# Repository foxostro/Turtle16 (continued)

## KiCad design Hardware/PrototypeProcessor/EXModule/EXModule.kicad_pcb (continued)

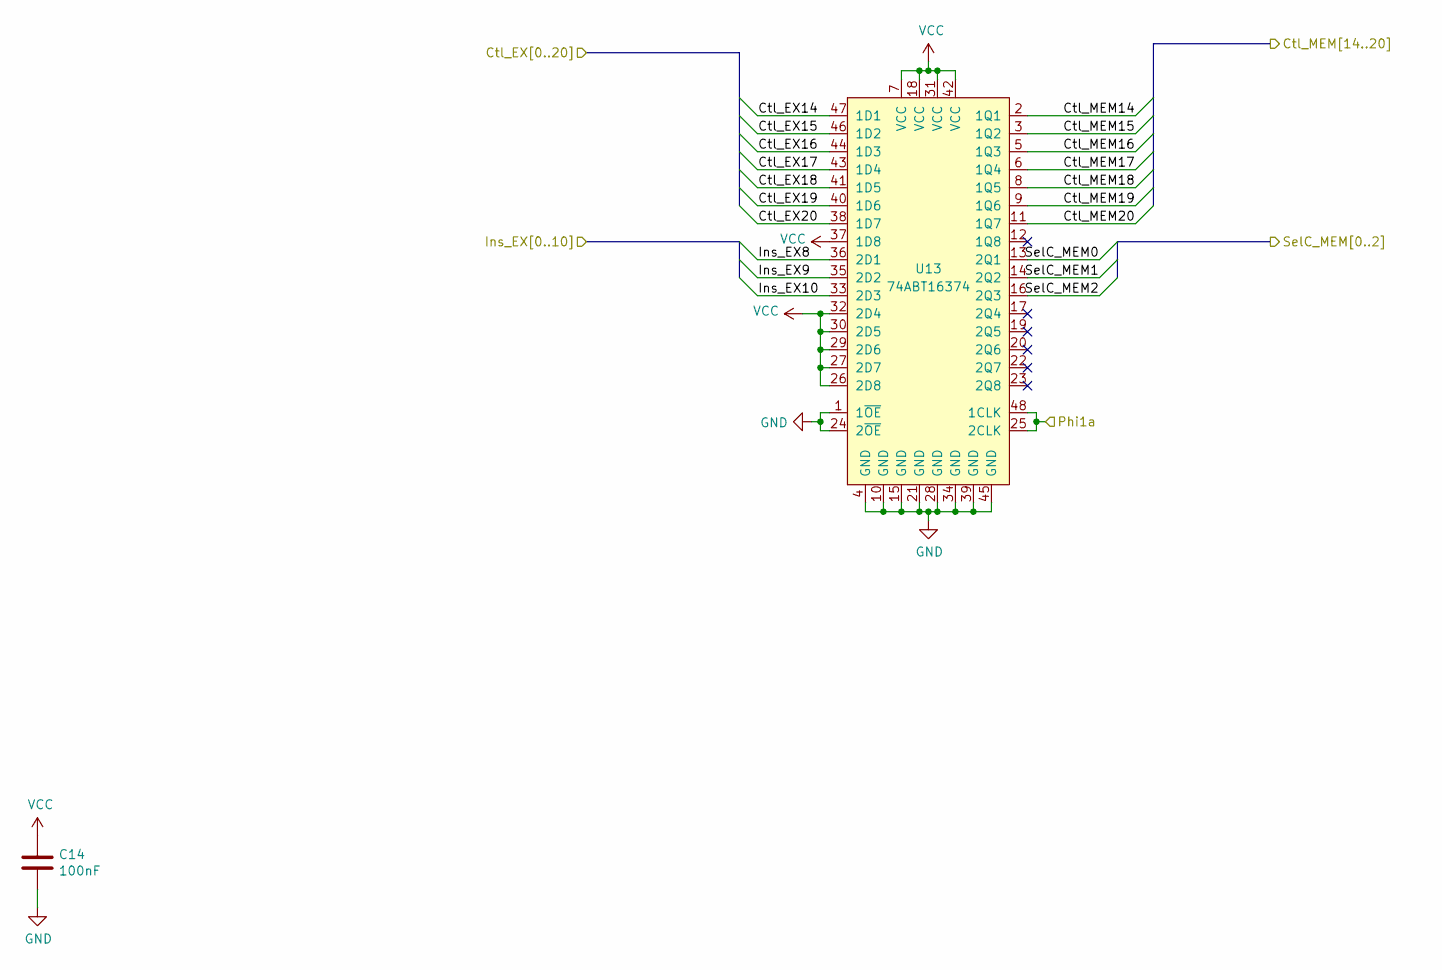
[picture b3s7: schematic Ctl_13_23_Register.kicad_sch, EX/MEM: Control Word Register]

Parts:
C14: 100nF; C_0603_1608Metric_Pad1.08x0.95mm_HandSolder
U13: 74ABT16374; TSSOP-48_6.1x12.5mm_P0.5mm

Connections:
/EX Prototype Inputs/Ctl_EX14: U13.47 (1D1); also elsewhere on the board
/EX Prototype Inputs/Ctl_EX15: U13.46 (1D2); also elsewhere on the board
/EX Prototype Inputs/Ctl_EX16: U13.44 (1D3); also elsewhere on the board
/EX Prototype Inputs/Ctl_EX17: U13.43 (1D4); also elsewhere on the board
/EX Prototype Inputs/Ctl_EX18: U13.41 (1D5); also elsewhere on the board
/EX Prototype Inputs/Ctl_EX19: U13.40 (1D6); also elsewhere on the board
/EX Prototype Inputs/Ctl_EX20: U13.38 (1D7); also elsewhere on the board
/EX Prototype Inputs/Ins_EX8: U13.36 (2D1); also elsewhere on the board
/EX Prototype Inputs/Ins_EX9: U13.35 (2D2); also elsewhere on the board
/EX Prototype Inputs/Ins_EX10: U13.33 (2D3); also elsewhere on the board
/EX Prototype Inputs/Phi1a: U13.25 (2CLK), U13.48 (1CLK); also elsewhere on the board
/EX Prototype Outputs/Ctl_MEM14: U13.2 (1Q1); also elsewhere on the board
/EX Prototype Outputs/Ctl_MEM15: U13.3 (1Q2); also elsewhere on the board
/EX Prototype Outputs/Ctl_MEM16: U13.5 (1Q3); also elsewhere on the board
/EX Prototype Outputs/Ctl_MEM17: U13.6 (1Q4); also elsewhere on the board
/EX Prototype Outputs/Ctl_MEM18: U13.8 (1Q5); also elsewhere on the board
/EX Prototype Outputs/Ctl_MEM19: U13.9 (1Q6); also elsewhere on the board
/EX Prototype Outputs/Ctl_MEM20: U13.11 (1Q7); also elsewhere on the board
/EX Prototype Outputs/SelC_MEM0: U13.13 (2Q1); also elsewhere on the board
/EX Prototype Outputs/SelC_MEM1: U13.14 (2Q2); also elsewhere on the board
/EX Prototype Outputs/SelC_MEM2: U13.16 (2Q3); also elsewhere on the board
GND: C14.2, U13.1 (1~OE), U13.4 (GND), U13.10 (GND), U13.15 (GND), U13.21 (GND), U13.24 (2~OE), U13.28 (GND), U13.34 (GND), U13.39 (GND), U13.45 (GND); also elsewhere on the board
VCC: C14.1, U13.7 (VCC), U13.18 (VCC), U13.26 (2D8), U13.27 (2D7), U13.29 (2D6), U13.30 (2D5), U13.31 (VCC), U13.32 (2D4), U13.37 (1D8), U13.42 (VCC); also elsewhere on the board

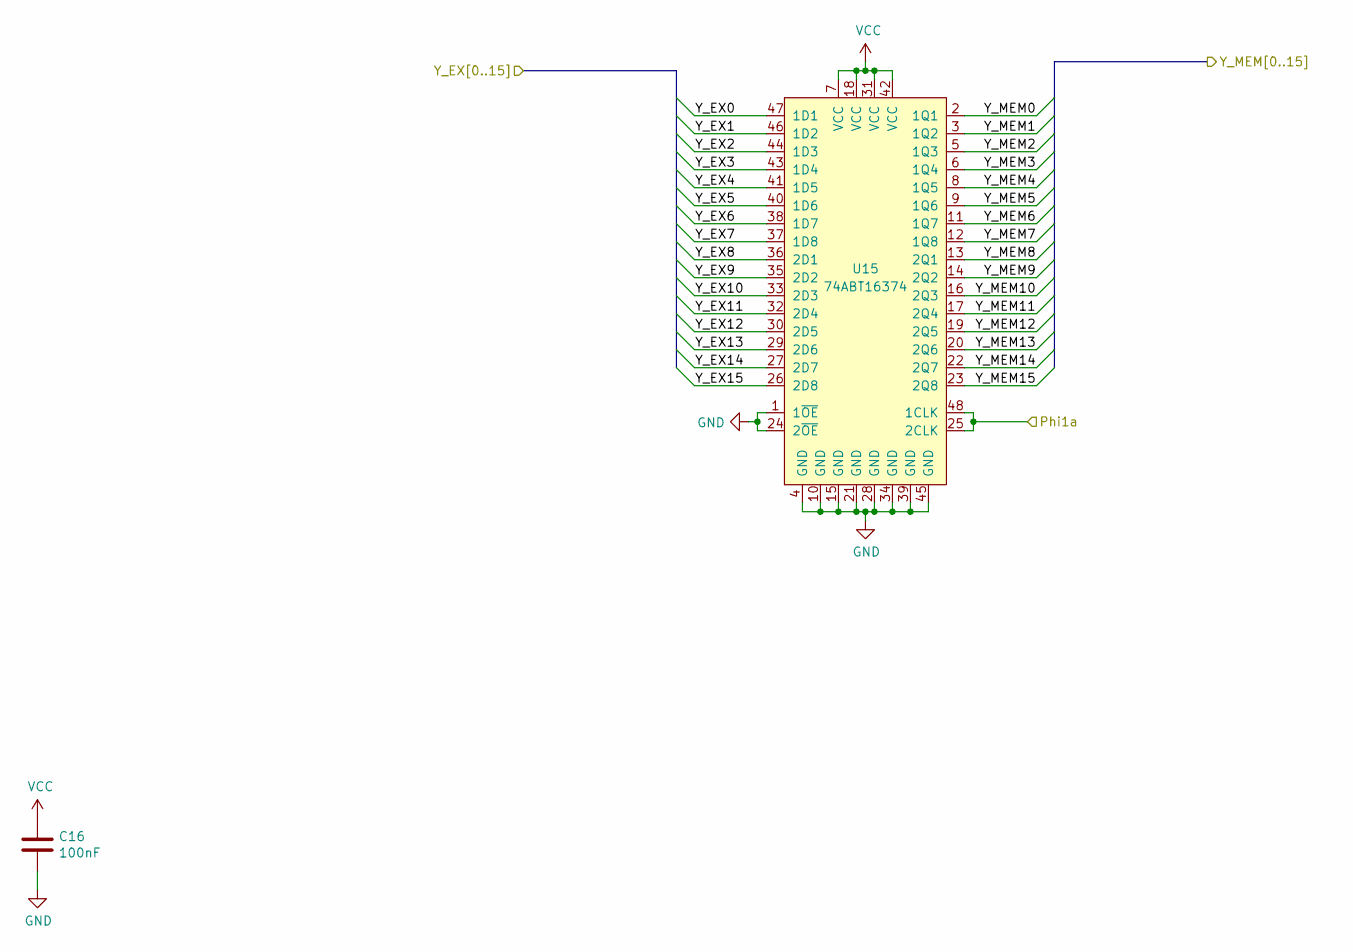
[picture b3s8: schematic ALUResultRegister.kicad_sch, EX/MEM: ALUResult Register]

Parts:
C16: 100nF; C_0603_1608Metric_Pad1.08x0.95mm_HandSolder
U15: 74ABT16374; TSSOP-48_6.1x12.5mm_P0.5mm

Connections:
/EX Prototype Inputs/Phi1a: U15.25 (2CLK), U15.48 (1CLK); also elsewhere on the board
/EX Prototype Outputs/Y_EX0: U15.47 (1D1); also elsewhere on the board
/EX Prototype Outputs/Y_EX1: U15.46 (1D2); also elsewhere on the board
/EX Prototype Outputs/Y_EX2: U15.44 (1D3); also elsewhere on the board
/EX Prototype Outputs/Y_EX3: U15.43 (1D4); also elsewhere on the board
/EX Prototype Outputs/Y_EX4: U15.41 (1D5); also elsewhere on the board
/EX Prototype Outputs/Y_EX5: U15.40 (1D6); also elsewhere on the board
/EX Prototype Outputs/Y_EX6: U15.38 (1D7); also elsewhere on the board
/EX Prototype Outputs/Y_EX7: U15.37 (1D8); also elsewhere on the board
/EX Prototype Outputs/Y_EX8: U15.36 (2D1); also elsewhere on the board
/EX Prototype Outputs/Y_EX9: U15.35 (2D2); also elsewhere on the board
/EX Prototype Outputs/Y_EX10: U15.33 (2D3); also elsewhere on the board
/EX Prototype Outputs/Y_EX11: U15.32 (2D4); also elsewhere on the board
/EX Prototype Outputs/Y_EX12: U15.30 (2D5); also elsewhere on the board
/EX Prototype Outputs/Y_EX13: U15.29 (2D6); also elsewhere on the board
/EX Prototype Outputs/Y_EX14: U15.27 (2D7); also elsewhere on the board
/EX Prototype Outputs/Y_EX15: U15.26 (2D8); also elsewhere on the board
/EX Prototype Outputs/Y_MEM0: U15.2 (1Q1); also elsewhere on the board
/EX Prototype Outputs/Y_MEM1: U15.3 (1Q2); also elsewhere on the board
/EX Prototype Outputs/Y_MEM2: U15.5 (1Q3); also elsewhere on the board
/EX Prototype Outputs/Y_MEM3: U15.6 (1Q4); also elsewhere on the board
/EX Prototype Outputs/Y_MEM4: U15.8 (1Q5); also elsewhere on the board
/EX Prototype Outputs/Y_MEM5: U15.9 (1Q6); also elsewhere on the board
/EX Prototype Outputs/Y_MEM6: U15.11 (1Q7); also elsewhere on the board
/EX Prototype Outputs/Y_MEM7: U15.12 (1Q8); also elsewhere on the board
/EX Prototype Outputs/Y_MEM8: U15.13 (2Q1); also elsewhere on the board
/EX Prototype Outputs/Y_MEM9: U15.14 (2Q2); also elsewhere on the board
/EX Prototype Outputs/Y_MEM10: U15.16 (2Q3); also elsewhere on the board
/EX Prototype Outputs/Y_MEM11: U15.17 (2Q4); also elsewhere on the board
/EX Prototype Outputs/Y_MEM12: U15.19 (2Q5); also elsewhere on the board
/EX Prototype Outputs/Y_MEM13: U15.20 (2Q6); also elsewhere on the board
/EX Prototype Outputs/Y_MEM14: U15.22 (2Q7); also elsewhere on the board
/EX Prototype Outputs/Y_MEM15: U15.23 (2Q8); also elsewhere on the board
GND: C16.2, U15.1 (1~OE), U15.4 (GND), U15.10 (GND), U15.15 (GND), U15.21 (GND), U15.24 (2~OE), U15.28 (GND), U15.34 (GND), U15.39 (GND), U15.45 (GND); also elsewhere on the board
VCC: C16.1, U15.7 (VCC), U15.18 (VCC), U15.31 (VCC), U15.42 (VCC); also elsewhere on the board

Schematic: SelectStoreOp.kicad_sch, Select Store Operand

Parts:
C8, C9, C10, C11, C12: 100nF; C_0603_1608Metric_Pad1.08x0.95mm_HandSolder
U7, U9, U10, U11: 74AHCT16245; TSSOP-48_6.1x12.5mm_P0.5mm
U8: 74AHCT138; TSSOP-16_4.4x5mm_P0.65mm

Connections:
/EX Prototype Inputs/B0: U7.47 (1A1); also elsewhere on the board
/EX Prototype Inputs/B1: U7.46 (1A2); also elsewhere on the board
/EX Prototype Inputs/B2: U7.44 (1A3); also elsewhere on the board
/EX Prototype Inputs/B3: U7.43 (1A4); also elsewhere on the board
/EX Prototype Inputs/B4: U7.41 (1A5); also elsewhere on the board
/EX Prototype Inputs/B5: U7.40 (1A6); also elsewhere on the board
/EX Prototype Inputs/B6: U7.38 (1A7); also elsewhere on the board
/EX Prototype Inputs/B7: U7.37 (1A8); also elsewhere on the board
/EX Prototype Inputs/B8: U7.36 (2A1); also elsewhere on the board
/EX Prototype Inputs/B9: U7.35 (2A2); also elsewhere on the board
/EX Prototype Inputs/B10: U7.33 (2A3); also elsewhere on the board
/EX Prototype Inputs/B11: U7.32 (2A4); also elsewhere on the board
/EX Prototype Inputs/B12: U7.30 (2A5); also elsewhere on the board
/EX Prototype Inputs/B13: U7.29 (2A6); also elsewhere on the board
/EX Prototype Inputs/B14: U7.27 (2A7); also elsewhere on the board
/EX Prototype Inputs/B15: U7.26 (2A8); also elsewhere on the board
/EX Prototype Inputs/Ctl_EX1: U8.1 (A0); also elsewhere on the board
/EX Prototype Inputs/Ctl_EX2: U8.2 (A1); also elsewhere on the board
/EX Prototype Inputs/Ins_EX0: U10.47 (1A1), U11.36 (2A1); also elsewhere on the board
/EX Prototype Inputs/Ins_EX1: U10.46 (1A2), U11.35 (2A2); also elsewhere on the board
/EX Prototype Inputs/Ins_EX2: U10.44 (1A3), U11.33 (2A3); also elsewhere on the board
/EX Prototype Inputs/Ins_EX3: U10.43 (1A4), U11.32 (2A4); also elsewhere on the board
/EX Prototype Inputs/Ins_EX4: U10.41 (1A5), U11.30 (2A5); also elsewhere on the board
/EX Prototype Inputs/Ins_EX5: U10.40 (1A6), U11.29 (2A6); also elsewhere on the board
/EX Prototype Inputs/Ins_EX6: U10.38 (1A7), U11.27 (2A7); also elsewhere on the board
/EX Prototype Inputs/Ins_EX7: U10.26 (2A8), U10.27 (2A7), U10.29 (2A6), U10.30 (2A5), U10.32 (2A4), U10.33 (2A3), U10.35 (2A2), U10.36 (2A1), U10.37 (1A8), U11.26 (2A8); also elsewhere on the board
/EX Prototype Inputs/PC_EX0: U9.47 (1A1); also elsewhere on the board
/EX Prototype Inputs/PC_EX1: U9.46 (1A2); also elsewhere on the board
/EX Prototype Inputs/PC_EX2: U9.44 (1A3); also elsewhere on the board
/EX Prototype Inputs/PC_EX3: U9.43 (1A4); also elsewhere on the board
/EX Prototype Inputs/PC_EX4: U9.41 (1A5); also elsewhere on the board
/EX Prototype Inputs/PC_EX5: U9.40 (1A6); also elsewhere on the board
/EX Prototype Inputs/PC_EX6: U9.38 (1A7); also elsewhere on the board
/EX Prototype Inputs/PC_EX7: U9.37 (1A8); also elsewhere on the board
/EX Prototype Inputs/PC_EX8: U9.36 (2A1); also elsewhere on the board
/EX Prototype Inputs/PC_EX9: U9.35 (2A2); also elsewhere on the board
/EX Prototype Inputs/PC_EX10: U9.33 (2A3); also elsewhere on the board
/EX Prototype Inputs/PC_EX11: U9.32 (2A4); also elsewhere on the board
/EX Prototype Inputs/PC_EX12: U9.30 (2A5); also elsewhere on the board
/EX Prototype Inputs/PC_EX13: U9.29 (2A6); also elsewhere on the board
/EX Prototype Inputs/PC_EX14: U9.27 (2A7); also elsewhere on the board
/EX Prototype Inputs/PC_EX15: U9.26 (2A8); also elsewhere on the board
/EX/sheet5FD8D6EA/StoreOp_EX0: U7.2 (1B1), U9.2 (1B1), U10.2 (1B1), U11.2 (1B1); also elsewhere on the board
/EX/sheet5FD8D6EA/StoreOp_EX1: U7.3 (1B2), U9.3 (1B2), U10.3 (1B2), U11.3 (1B2); also elsewhere on the board
/EX/sheet5FD8D6EA/StoreOp_EX2: U7.5 (1B3), U9.5 (1B3), U10.5 (1B3), U11.5 (1B3); also elsewhere on the board
/EX/sheet5FD8D6EA/StoreOp_EX3: U7.6 (1B4), U9.6 (1B4), U10.6 (1B4), U11.6 (1B4); also elsewhere on the board
/EX/sheet5FD8D6EA/StoreOp_EX4: U7.8 (1B5), U9.8 (1B5), U10.8 (1B5), U11.8 (1B5); also elsewhere on the board
/EX/sheet5FD8D6EA/StoreOp_EX5: U7.9 (1B6), U9.9 (1B6), U10.9 (1B6), U11.9 (1B6); also elsewhere on the board
/EX/sheet5FD8D6EA/StoreOp_EX6: U7.11 (1B7), U9.11 (1B7), U10.11 (1B7), U11.11 (1B7); also elsewhere on the board
/EX/sheet5FD8D6EA/StoreOp_EX7: U7.12 (1B8), U9.12 (1B8), U10.12 (1B8), U11.12 (1B8); also elsewhere on the board
/EX/sheet5FD8D6EA/StoreOp_EX8: U7.13 (2B1), U9.13 (2B1), U10.13 (2B1), U11.13 (2B1); also elsewhere on the board
/EX/sheet5FD8D6EA/StoreOp_EX9: U7.14 (2B2), U9.14 (2B2), U10.14 (2B2), U11.14 (2B2); also elsewhere on the board
/EX/sheet5FD8D6EA/StoreOp_EX10: U7.16 (2B3), U9.16 (2B3), U10.16 (2B3), U11.16 (2B3); also elsewhere on the board
/EX/sheet5FD8D6EA/StoreOp_EX11: U7.17 (2B4), U9.17 (2B4), U10.17 (2B4), U11.17 (2B4); also elsewhere on the board
/EX/sheet5FD8D6EA/StoreOp_EX12: U7.19 (2B5), U9.19 (2B5), U10.19 (2B5), U11.19 (2B5); also elsewhere on the board
/EX/sheet5FD8D6EA/StoreOp_EX13: U7.20 (2B6), U9.20 (2B6), U10.20 (2B6), U11.20 (2B6); also elsewhere on the board
/EX/sheet5FD8D6EA/StoreOp_EX14: U7.22 (2B7), U9.22 (2B7), U10.22 (2B7), U11.22 (2B7); also elsewhere on the board
/EX/sheet5FD8D6EA/StoreOp_EX15: U7.23 (2B8), U9.23 (2B8), U10.23 (2B8), U11.23 (2B8); also elsewhere on the board
GND: C8.2, C9.2, C10.2, C11.2, C12.2, U7.4 (GND), U7.10 (GND), U7.15 (GND), U7.21 (GND), U7.28 (GND), U7.34 (GND), U7.39 (GND), U7.45 (GND), U8.3 (A2), U8.4 (E1), U8.5 (E2), U8.8 (GND), U9.4 (GND), U9.10 (GND), U9.15 (GND), U9.21 (GND), U9.28 (GND), U9.34 (GND), U9.39 (GND), U9.45 (GND), U10.4 (GND), U10.10 (GND), U10.15 (GND), U10.21 (GND), U10.28 (GND), U10.34 (GND), U10.39 (GND), U10.45 (GND), U11.4 (GND), U11.10 (GND), U11.15 (GND), U11.21 (GND), U11.28 (GND), U11.34 (GND), U11.37 (1A8), U11.38 (1A7), U11.39 (GND), U11.40 (1A6), U11.41 (1A5), U11.43 (1A4), U11.44 (1A3), U11.45 (GND), U11.46 (1A2), U11.47 (1A1); also elsewhere on the board
unnamed: U7.25 (2~OE), U7.48 (1~OE), U8.15 (O0)
unnamed: U8.14 (O1), U9.25 (2~OE), U9.48 (1~OE)
unnamed: U8.13 (O2), U10.25 (2~OE), U10.48 (1~OE)
unnamed: U8.12 (O3), U11.25 (2~OE), U11.48 (1~OE)
VCC: C8.1, C9.1, C10.1, C11.1, C12.1, U7.1 (1DIR), U7.7 (VCC), U7.18 (VCC), U7.24 (2DIR), U7.31 (VCC), U7.42 (VCC), U8.6 (E3), U8.16 (VCC), U9.1 (1DIR), U9.7 (VCC), U9.18 (VCC), U9.24 (2DIR), U9.31 (VCC), U9.42 (VCC), U10.1 (1DIR), U10.7 (VCC), U10.18 (VCC), U10.24 (2DIR), U10.31 (VCC), U10.42 (VCC), U11.1 (1DIR), U11.7 (VCC), U11.18 (VCC), U11.24 (2DIR), U11.31 (VCC), U11.42 (VCC); also elsewhere on the board

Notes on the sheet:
SelStoreOp=0 —> Select Register B SelStoreOp=1 —> Select PC+1 (return address) SelStoreOp=2 —> Select 8-bit Immediate Value SelStoreOp=3 —> Select 8-bit Immediate Value << 8

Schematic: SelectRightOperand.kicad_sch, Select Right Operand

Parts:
C3, C4, C5, C6, C7: 100nF; C_0603_1608Metric_Pad1.08x0.95mm_HandSolder
U2, U3, U5, U6: 74AHCT16245; TSSOP-48_6.1x12.5mm_P0.5mm
U4: 74AHCT138; TSSOP-16_4.4x5mm_P0.65mm

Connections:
/EX Prototype Inputs/B0: U2.47 (1A1); also elsewhere on the board
/EX Prototype Inputs/B1: U2.46 (1A2); also elsewhere on the board
/EX Prototype Inputs/B2: U2.44 (1A3); also elsewhere on the board
/EX Prototype Inputs/B3: U2.43 (1A4); also elsewhere on the board
/EX Prototype Inputs/B4: U2.41 (1A5); also elsewhere on the board
/EX Prototype Inputs/B5: U2.40 (1A6); also elsewhere on the board
/EX Prototype Inputs/B6: U2.38 (1A7); also elsewhere on the board
/EX Prototype Inputs/B7: U2.37 (1A8); also elsewhere on the board
/EX Prototype Inputs/B8: U2.36 (2A1); also elsewhere on the board
/EX Prototype Inputs/B9: U2.35 (2A2); also elsewhere on the board
/EX Prototype Inputs/B10: U2.33 (2A3); also elsewhere on the board
/EX Prototype Inputs/B11: U2.32 (2A4); also elsewhere on the board
/EX Prototype Inputs/B12: U2.30 (2A5); also elsewhere on the board
/EX Prototype Inputs/B13: U2.29 (2A6); also elsewhere on the board
/EX Prototype Inputs/B14: U2.27 (2A7); also elsewhere on the board
/EX Prototype Inputs/B15: U2.26 (2A8); also elsewhere on the board
/EX Prototype Inputs/Ctl_EX3: U4.1 (A0); also elsewhere on the board
/EX Prototype Inputs/Ctl_EX4: U4.2 (A1); also elsewhere on the board
/EX Prototype Inputs/Ins_EX0: U3.47 (1A1), U5.47 (1A1), U6.47 (1A1); also elsewhere on the board
/EX Prototype Inputs/Ins_EX1: U3.46 (1A2), U5.46 (1A2), U6.46 (1A2); also elsewhere on the board
/EX Prototype Inputs/Ins_EX2: U3.44 (1A3), U6.44 (1A3); also elsewhere on the board
/EX Prototype Inputs/Ins_EX3: U3.43 (1A4), U6.43 (1A4); also elsewhere on the board
/EX Prototype Inputs/Ins_EX4: U3.26 (2A8), U3.27 (2A7), U3.29 (2A6), U3.30 (2A5), U3.32 (2A4), U3.33 (2A3), U3.35 (2A2), U3.36 (2A1), U3.37 (1A8), U3.38 (1A7), U3.40 (1A6), U3.41 (1A5), U6.41 (1A5); also elsewhere on the board
/EX Prototype Inputs/Ins_EX5: U6.40 (1A6); also elsewhere on the board
/EX Prototype Inputs/Ins_EX6: U6.38 (1A7); also elsewhere on the board
/EX Prototype Inputs/Ins_EX7: U6.37 (1A8); also elsewhere on the board
/EX Prototype Inputs/Ins_EX8: U5.44 (1A3), U6.36 (2A1); also elsewhere on the board
/EX Prototype Inputs/Ins_EX9: U5.43 (1A4), U6.35 (2A2); also elsewhere on the board
/EX Prototype Inputs/Ins_EX10: U5.26 (2A8), U5.27 (2A7), U5.29 (2A6), U5.30 (2A5), U5.32 (2A4), U5.33 (2A3), U5.35 (2A2), U5.36 (2A1), U5.37 (1A8), U5.38 (1A7), U5.40 (1A6), U5.41 (1A5), U6.26 (2A8), U6.27 (2A7), U6.29 (2A6), U6.30 (2A5), U6.32 (2A4), U6.33 (2A3); also elsewhere on the board
/EX/ALU/RightOp0: U2.2 (1B1), U3.2 (1B1), U5.2 (1B1), U6.2 (1B1); also elsewhere on the board
/EX/ALU/RightOp1: U2.3 (1B2), U3.3 (1B2), U5.3 (1B2), U6.3 (1B2); also elsewhere on the board
/EX/ALU/RightOp2: U2.5 (1B3), U3.5 (1B3), U5.5 (1B3), U6.5 (1B3); also elsewhere on the board
/EX/ALU/RightOp3: U2.6 (1B4), U3.6 (1B4), U5.6 (1B4), U6.6 (1B4); also elsewhere on the board
/EX/ALU/RightOp4: U2.8 (1B5), U3.8 (1B5), U5.8 (1B5), U6.8 (1B5); also elsewhere on the board
/EX/ALU/RightOp5: U2.9 (1B6), U3.9 (1B6), U5.9 (1B6), U6.9 (1B6); also elsewhere on the board
/EX/ALU/RightOp6: U2.11 (1B7), U3.11 (1B7), U5.11 (1B7), U6.11 (1B7); also elsewhere on the board
/EX/ALU/RightOp7: U2.12 (1B8), U3.12 (1B8), U5.12 (1B8), U6.12 (1B8); also elsewhere on the board
/EX/ALU/RightOp8: U2.13 (2B1), U3.13 (2B1), U5.13 (2B1), U6.13 (2B1); also elsewhere on the board
/EX/ALU/RightOp9: U2.14 (2B2), U3.14 (2B2), U5.14 (2B2), U6.14 (2B2); also elsewhere on the board
/EX/ALU/RightOp10: U2.16 (2B3), U3.16 (2B3), U5.16 (2B3), U6.16 (2B3); also elsewhere on the board
/EX/ALU/RightOp11: U2.17 (2B4), U3.17 (2B4), U5.17 (2B4), U6.17 (2B4); also elsewhere on the board
/EX/ALU/RightOp12: U2.19 (2B5), U3.19 (2B5), U5.19 (2B5), U6.19 (2B5); also elsewhere on the board
/EX/ALU/RightOp13: U2.20 (2B6), U3.20 (2B6), U5.20 (2B6), U6.20 (2B6); also elsewhere on the board
/EX/ALU/RightOp14: U2.22 (2B7), U3.22 (2B7), U5.22 (2B7), U6.22 (2B7); also elsewhere on the board
/EX/ALU/RightOp15: U2.23 (2B8), U3.23 (2B8), U5.23 (2B8), U6.23 (2B8); also elsewhere on the board
GND: C3.2, C4.2, C5.2, C6.2, C7.2, U2.4 (GND), U2.10 (GND), U2.15 (GND), U2.21 (GND), U2.28 (GND), U2.34 (GND), U2.39 (GND), U2.45 (GND), U3.4 (GND), U3.10 (GND), U3.15 (GND), U3.21 (GND), U3.28 (GND), U3.34 (GND), U3.39 (GND), U3.45 (GND), U4.3 (A2), U4.4 (E1), U4.5 (E2), U4.8 (GND), U5.4 (GND), U5.10 (GND), U5.15 (GND), U5.21 (GND), U5.28 (GND), U5.34 (GND), U5.39 (GND), U5.45 (GND), U6.4 (GND), U6.10 (GND), U6.15 (GND), U6.21 (GND), U6.28 (GND), U6.34 (GND), U6.39 (GND), U6.45 (GND); also elsewhere on the board
unnamed: U2.25 (2~OE), U2.48 (1~OE), U4.15 (O0)
unnamed: U3.25 (2~OE), U3.48 (1~OE), U4.14 (O1)
unnamed: U4.12 (O3), U6.25 (2~OE), U6.48 (1~OE)
unnamed: U4.13 (O2), U5.25 (2~OE), U5.48 (1~OE)
VCC: C3.1, C4.1, C5.1, C6.1, C7.1, U2.1 (1DIR), U2.7 (VCC), U2.18 (VCC), U2.24 (2DIR), U2.31 (VCC), U2.42 (VCC), U3.1 (1DIR), U3.7 (VCC), U3.18 (VCC), U3.24 (2DIR), U3.31 (VCC), U3.42 (VCC), U4.6 (E3), U4.16 (VCC), U5.1 (1DIR), U5.7 (VCC), U5.18 (VCC), U5.24 (2DIR), U5.31 (VCC), U5.42 (VCC), U6.1 (1DIR), U6.7 (VCC), U6.18 (VCC), U6.24 (2DIR), U6.31 (VCC), U6.42 (VCC); also elsewhere on the board

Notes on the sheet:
SelRightOp=0 —> Select Register B SelRightOp=1 —> Select Immediate ins[4:0] SelRightOp=2 —> Select Immediate ins[10:8, 1:0] SelRightOp=3 —> Select Immediate ins[10:0]

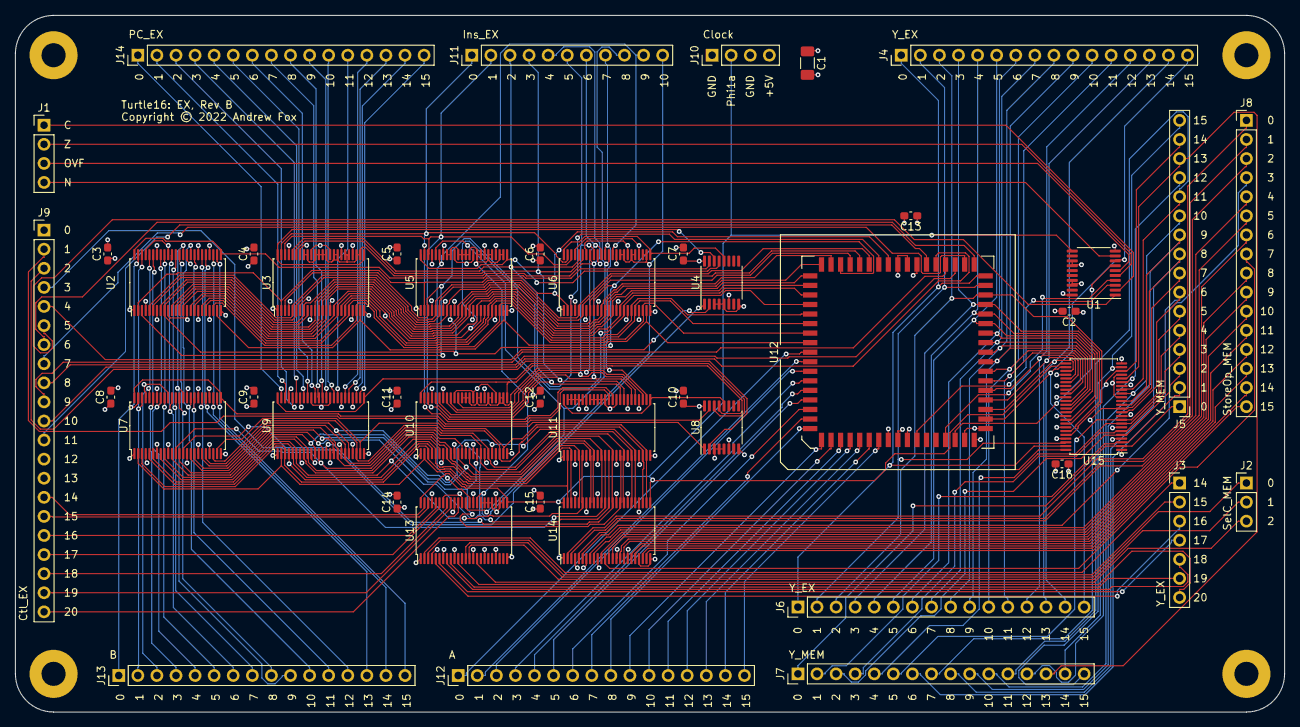
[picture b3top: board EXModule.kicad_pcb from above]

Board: 4 copper layers, 168.9 x 92.7 mm, 49 parts (0 on the bottom side), 185 nets.

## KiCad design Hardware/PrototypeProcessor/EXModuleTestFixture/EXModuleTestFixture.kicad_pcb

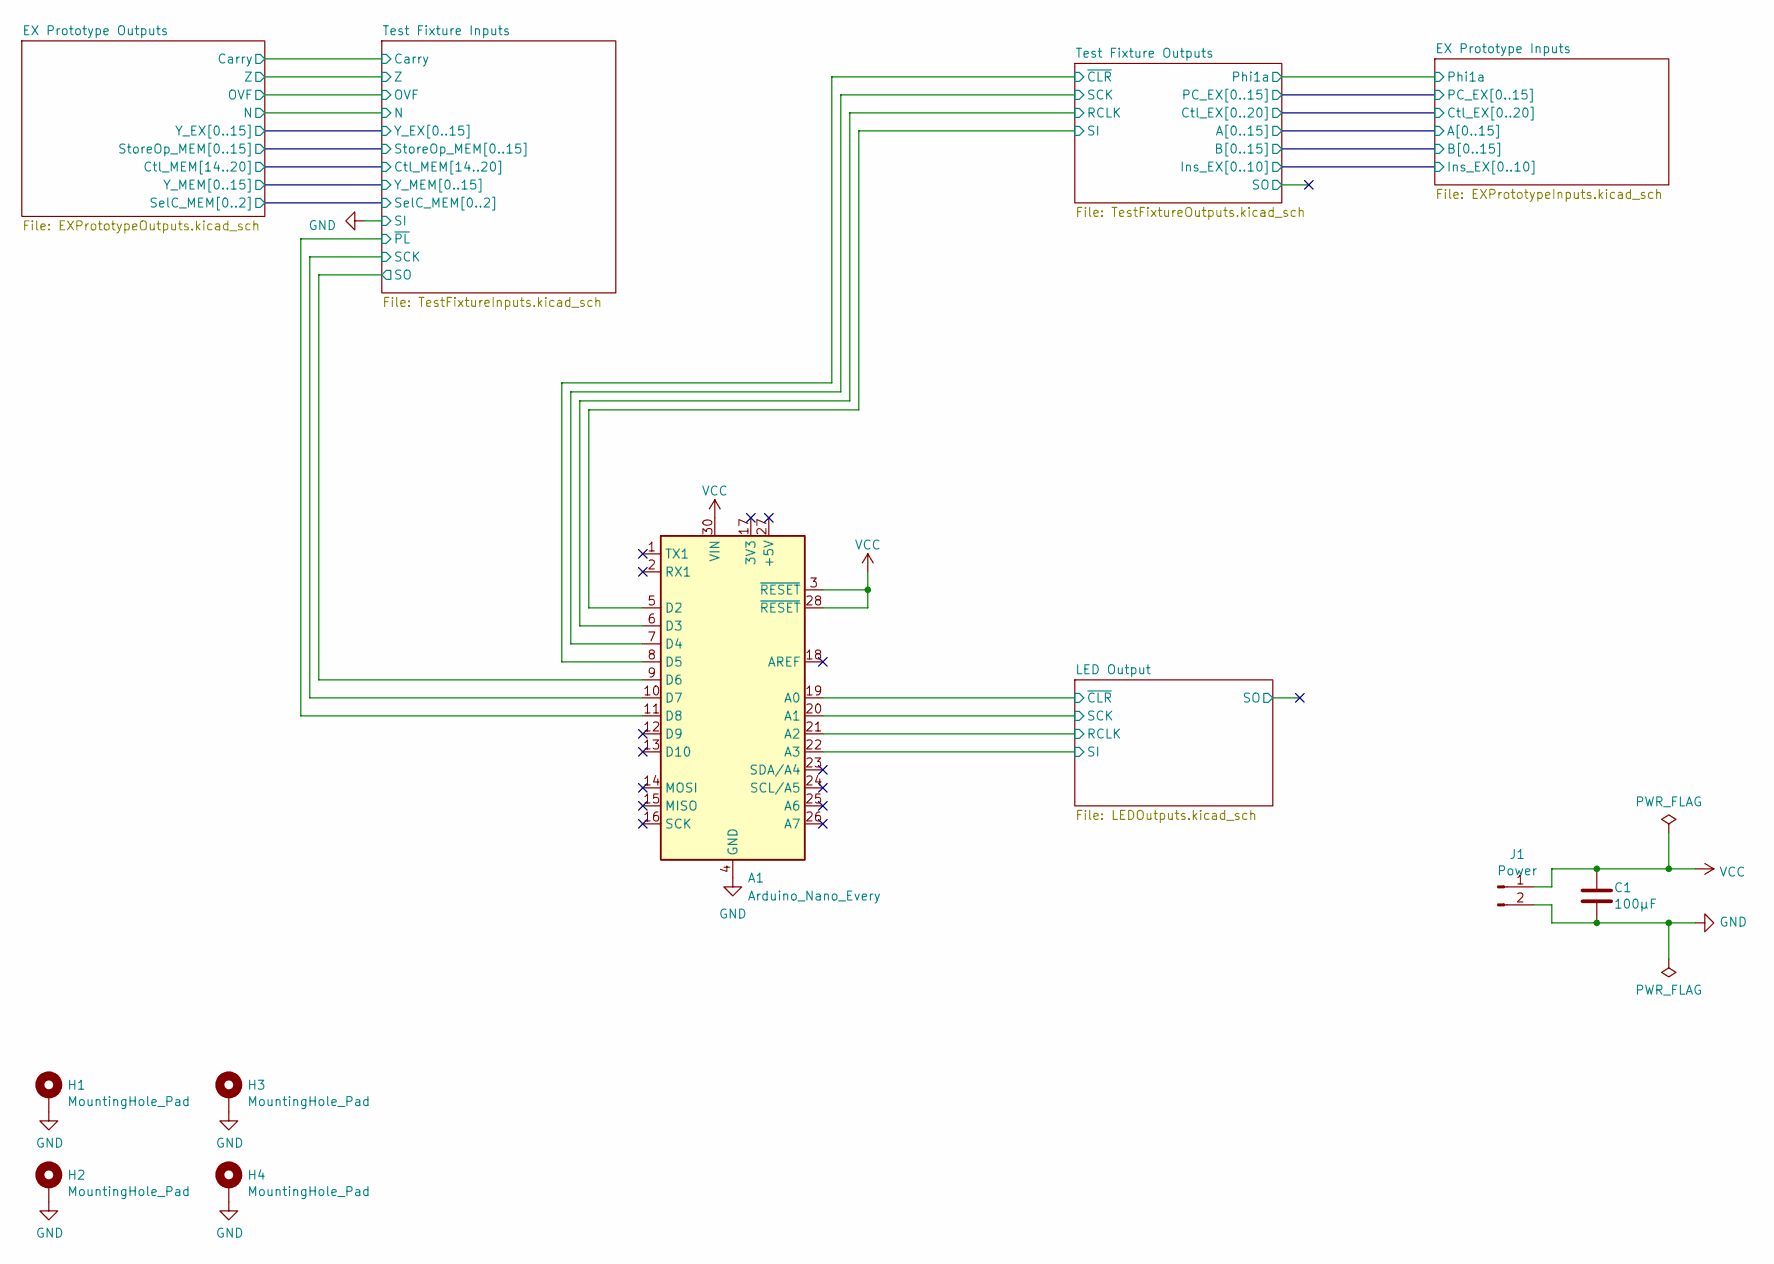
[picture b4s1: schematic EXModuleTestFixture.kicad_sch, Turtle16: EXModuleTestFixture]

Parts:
A1: Arduino_Nano_Every; Arduino_Nano
C1: 100µF; C_1206_3216Metric_Pad1.33x1.80mm_HandSolder
H1, H2, H3, H4: MountingHole_Pad; MountingHole_3.2mm_M3_Pad
J1: Power; 172448-0002

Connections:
/LED Output/RCLK: A1.21 (A2); also elsewhere on the board
/LED Output/SCK: A1.20 (A1); also elsewhere on the board
/LED Output/SI: A1.22 (A3); also elsewhere on the board
/LED Output/~CLR: A1.19 (A0); also elsewhere on the board
/Test Fixture Inputs/SCK: A1.10 (D7); also elsewhere on the board
/Test Fixture Inputs/SO: A1.9 (D6); also elsewhere on the board
/Test Fixture Inputs/~PL: A1.11 (D8); also elsewhere on the board
/Test Fixture Outputs/RCLK: A1.6 (D3); also elsewhere on the board
/Test Fixture Outputs/SCK: A1.7 (D4); also elsewhere on the board
/Test Fixture Outputs/SI: A1.5 (D2); also elsewhere on the board
/Test Fixture Outputs/~CLR: A1.8 (D5); also elsewhere on the board
GND: A1.4 (GND), A1.29 (GND), C1.2, H1.1, H2.1, H3.1, H4.1, J1.2; also elsewhere on the board
VCC: A1.3 (~RESET), A1.28 (~RESET), A1.30 (VIN), C1.1, J1.1; also elsewhere on the board
